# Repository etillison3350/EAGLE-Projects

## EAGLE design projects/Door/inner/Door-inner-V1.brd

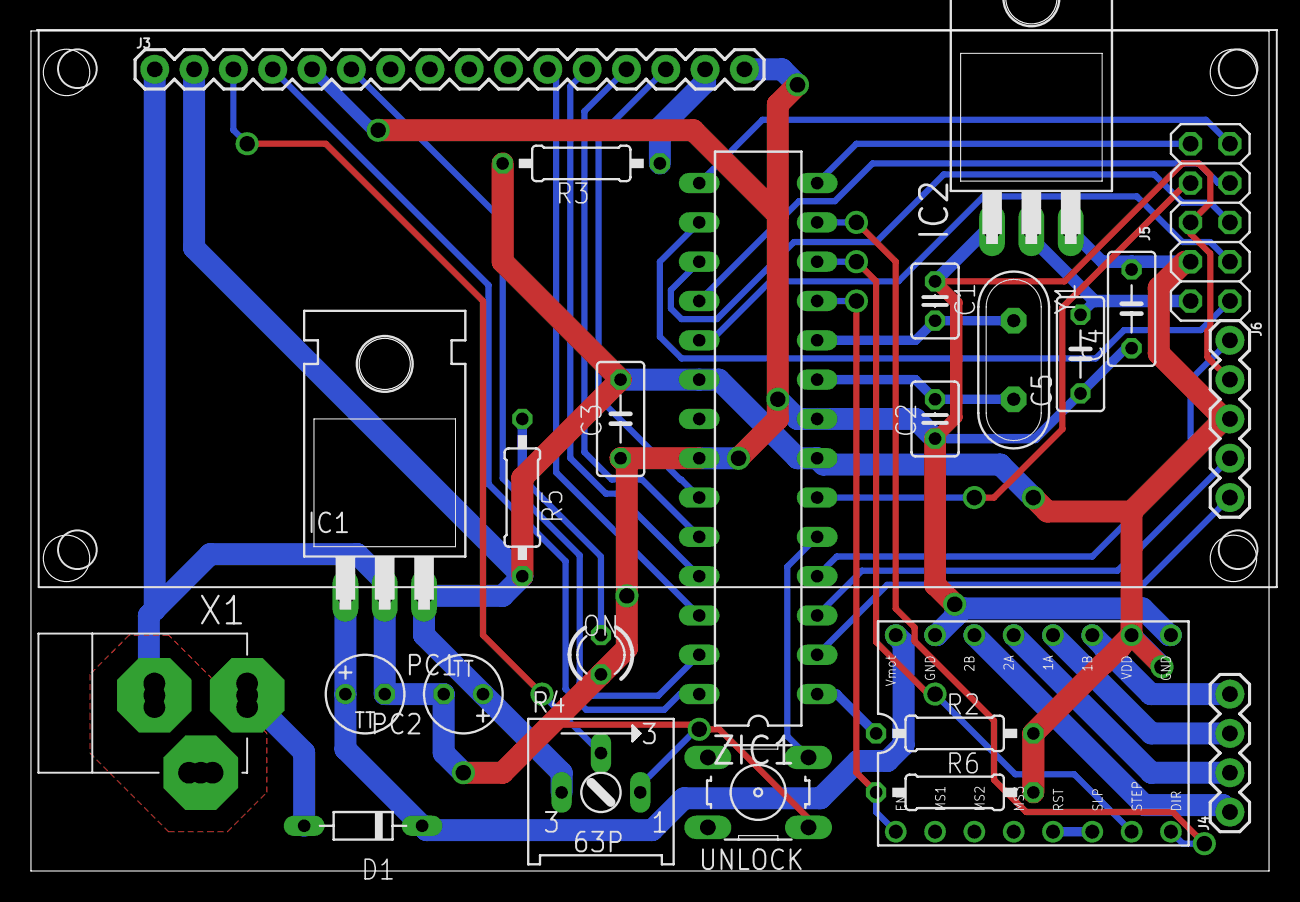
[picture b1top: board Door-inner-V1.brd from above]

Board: 2 copper layers, 80.0 x 54.3 mm, 25 parts (0 on the bottom side), 36 nets.

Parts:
C1, C2: 22p; C025-030X050
C3, C4: 100n; C050-030X075
C5: 1u; C050-030X075
D1: M7; D-7.5
IC1: 7815T; TO220H
IC2: 317T; TO220H
J3: LCD_4PIN; LCD-16X2
J4: 1X04
J5: 2X05
J6: 1X05
ON: LED3MM
PC1, PC2: 47u; TT2D5
R2, R6: 10k; 0207/10
R3: 220; 0207/10
R4: S63P
R5: 470; 0207/10
U$1: A4988BREAKOUT
UNLOCK: B3F-10XX
X1: POWERSUPPLY_DC21MMX; POWERSUPPLY_DC-21MM
Y1: 16MHz; QS
ZIC1: ATMEGA8; DIL28-3

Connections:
+3V3: C5.2, IC2.2, J5.2
+5V: C3.2, C4.2, IC1.3, IC2.3, J3.2, J5.4, J6.3, PC2.+, R2.2, R3.2, R4.E, R5.2, R6.2, U$1.VDD, ZIC1.7, ZIC1.20
BUZ: J5.10, ZIC1.14
D4: J3.11, ZIC1.26
D5: J3.12, ZIC1.25
D6: J3.13, ZIC1.24
D7: J3.14, ZIC1.23
GND: C1.1, C2.1, C3.1, C4.1, C5.1, IC1.2, IC2.1, J3.1, J3.5, J3.16, J5.6, J6.2, ON.K, PC1.-, PC2.-, R4.A, U$1.GND, U$1.GND@0, UNLOCK.1, X1.1, X1.3, ZIC1.8, ZIC1.22
LCD-EN: J3.6, ZIC1.27
LCD-RS: J3.4, ZIC1.28
M-DIR: U$1.DIR, ZIC1.13
M-EN: R6.1, U$1.EN, ZIC1.11
M-STP: U$1.STEP, ZIC1.12
MISO: J5.7, ZIC1.18
MOSI: J5.5, ZIC1.17
unnamed: J6.1, ZIC1.4
unnamed: J6.4, ZIC1.3
unnamed: J6.5, ZIC1.2
unnamed: J3.15, R3.1
unnamed: J3.3, R4.S
unnamed: ON.A, R5.1
unnamed: U$1.RST, U$1.SLP
unnamed: J4.1, U$1.2B
unnamed: J4.2, U$1.2A
unnamed: J4.3, U$1.1A
unnamed: J4.4, U$1.1B
unnamed: UNLOCK.3, ZIC1.5
PWRIN: D1.A, X1.2
RESET: R2.1, ZIC1.1
RST: J5.9, ZIC1.15
SCK: J5.3, ZIC1.19
SDA: J5.1, ZIC1.16
STATUS: J5.8, ZIC1.6
VIN: D1.C, IC1.1, PC1.+, U$1.VMOT
XTAL1: C2.2, Y1.2, ZIC1.9
XTAL2: C1.2, Y1.1, ZIC1.10

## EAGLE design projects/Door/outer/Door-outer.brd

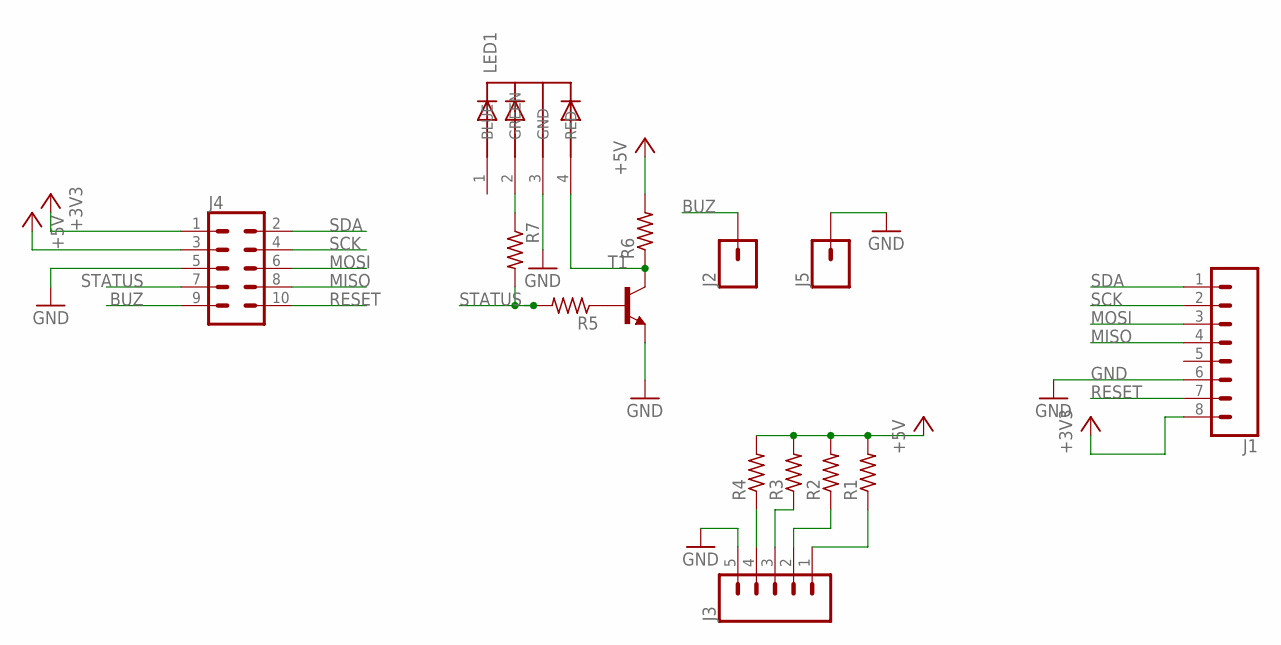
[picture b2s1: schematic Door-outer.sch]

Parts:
J1: CONN_08"; 1X08
J2, J5: CONN_01PTH_NO_SILK_YES_STOP; 1X01_NO_SILK
J3: CONN_05; 1X05
J4: CONN_05X2PTH; 2X5
LED1: 5MMRGBLED; LED5MMRGB
R1, R2, R3, R4, R5, R6, R7: R-US_R1206; R1206
T1: MPS2222A-NPN-TO92-CBE; TO92-CBE

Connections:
+3V3: J1.8, J4.1
+5V: J4.3, R1.2, R2.2, R3.2, R4.2, R6.2
BUZ: J2.1, J4.9
GND: J1.6, J3.5, J4.5, J5.1, LED1.3 (GND), T1.E
MISO: J1.4, J4.8
MOSI: J1.3, J4.6
unnamed: LED1.2 (GREEN), R7.1
unnamed: J3.1, R1.1
unnamed: J3.2, R2.1
unnamed: J3.3, R3.1
unnamed: J3.4, R4.1
unnamed: LED1.4 (RED), R6.1, T1.C
unnamed: R5.1, T1.B
RESET: J1.7, J4.10
SCK: J1.2, J4.4
SDA: J1.1, J4.2
STATUS: J4.7, R5.2, R7.2

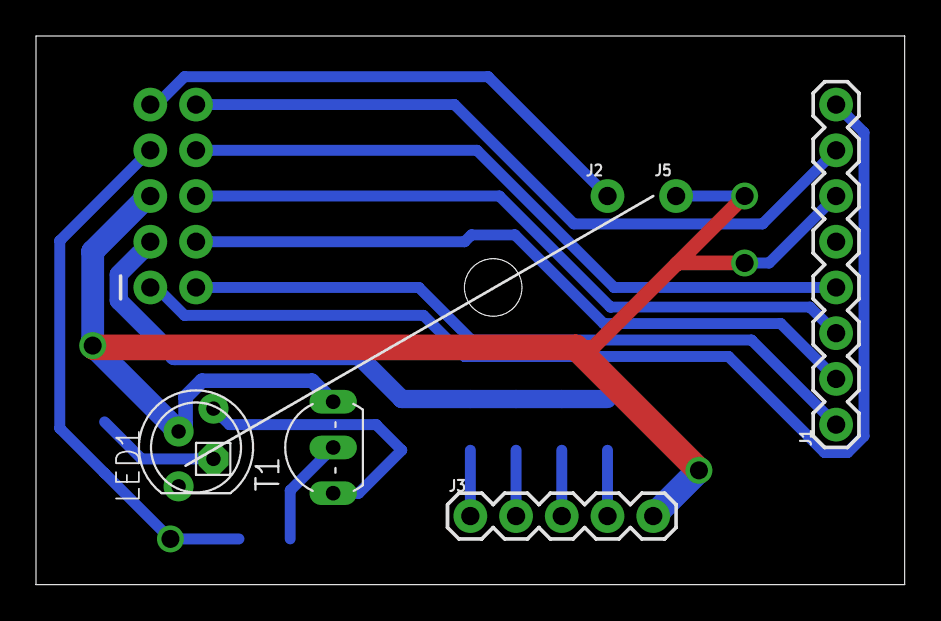
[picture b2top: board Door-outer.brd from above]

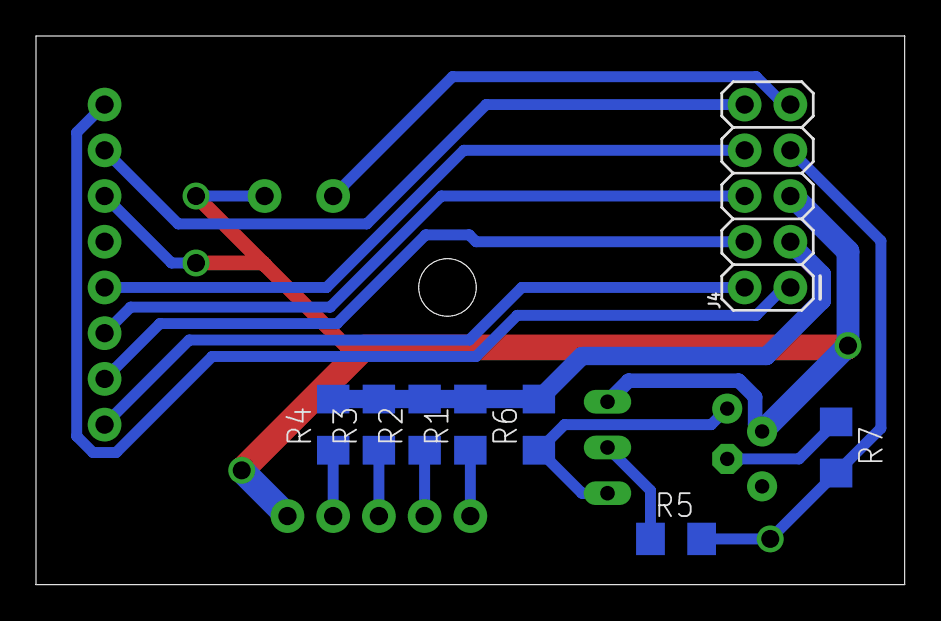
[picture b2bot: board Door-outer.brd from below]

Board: 2 copper layers, 48.3 x 30.5 mm, 14 parts (8 on the bottom side), 17 nets.

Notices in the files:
parts and their libraries:
SparkFun-Connectors: Licensing: Creative Commons ShareAlike 4.0 International - https://creativecommons.org/licenses/by-sa/4.0
